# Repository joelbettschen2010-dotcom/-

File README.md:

> **Weitere Projekte in diesem Repo:** [🤠 Wild West — Minecraft-Mod](westernmod/) für
> Minecraft Java 1.21.1 (Fabric).

# 🚲 Velo Navi Schweiz

Eine Velo-/E-Bike-Navigations-App für die **ganze Schweiz**. Sie schlägt
mehrere Routen vor, berechnet die Fahrzeit **physikalisch** (inkl. Steigung
und Velo-Typ) und **lernt dein persönliches Tempo** aus deinem Feedback nach
jeder Fahrt.

Läuft als **einzelne Web-App ohne Server** – einfach `index.html` im Browser
öffnen (oder in der Claude-App als Vorschau).

## Funktionen

- **Ganze Schweiz** – Ortssuche über swisstopo/geo.admin.ch oder Klick auf die Karte.
- **Mehrere Routenvorschläge** – Alternativrouten + optional andere Fahrstile als Varianten.
- **Velo-Typ wählbar** – **Velo**, **E-Bike 25** (Abregelung 25 km/h),
  **E-Bike 45** (S-Pedelec, 45 km/h). Der Motor wird im Zeitmodell berücksichtigt.
- **Routen-Stil** – **Trekking/Stadt**, **Rennvelo**, **Gravel**, **MTB Trail**
  (eigene BRouter-Profile mit passenden Untergründen).
- **Höhenberechnung** – die Steigung jedes Streckenabschnitts fliesst in die Zeit ein
  (bergauf dauert länger, bergab schneller), mit Höhenprofil-Diagramm.
- **Routenbeschreibung** – Anteil Strasse / Veloweg / Schotter / Wald / Trail,
  Höhenmeter ↑↓ und maximale Steigung pro Route.
- **Tempo-Feedback & Kalibrierung** – nach jeder Fahrt angeben „war schneller/langsamer".
  Die App passt den Tempo-Faktor **pro Velo-Typ** an und speichert ihn lokal.
- **GPX-Export** je Route.

## Bedienung

1. `index.html` im Browser öffnen.
2. Start & Ziel eingeben (Suche) oder auf die Karte klicken.
3. Velo-Typ, Routen-Stil und Tretleistung wählen.
4. **Routen berechnen** drücken.
5. Eine Route anklicken → Karte + Höhenprofil. Mit **🏁 Gefahren** Feedback geben.

## Wie die Zeit berechnet wird

Pro Streckenabschnitt wird die Gleichgewichts­geschwindigkeit aus der
Leistungs­gleichung gelöst:

```
P = v · ( Crr·m·g·cosθ  +  m·g·sinθ  +  ½·ρ·CdA·v² ) / η
```

- `Crr` Rollwiderstand (je nach Untergrund: Asphalt … Trail)
- `m` Gesamtmasse (Fahrer + Velo, je nach Velo-Typ)
- `θ` Steigungswinkel aus den Höhendaten
- `CdA` Luftwiderstandsfläche, `ρ` Luftdichte, `η` Antriebs­wirkungsgrad
- `P` = Tretleistung **+ Motorleistung** (E-Bike, nur unterhalb der Abregelgeschwindigkeit)

Das Ergebnis wird mit deinem persönlichen **Kalibrierungs­faktor** multipliziert.

## Datenquellen

- **Karten:** [swisstopo](https://www.swisstopo.admin.ch) WMTS (Landeskarte / Satellit)
- **Routing & Höhen:** [BRouter](https://brouter.de) (OSM-basiert, kostenlos)
- **Ortssuche:** geo.admin.ch SearchServer
- **Karten-Engine:** [Leaflet](https://leafletjs.com)

Alle Dienste sind kostenlos und benötigen keinen API-Schlüssel. Es ist eine
Internet­verbindung nötig (Kacheln, Routing, Suche).

## Dateien

| Datei | Zweck |
|-------|-------|
| `index.html` | Aufbau / UI |
| `style.css` | Gestaltung (dunkles Theme, responsiv) |
| `app.js` | Karte, Routing, Zeitmodell, Höhenprofil, Feedback |

## Hinweise / Limiten

- Der öffentliche BRouter-Server hat eine Fair-Use-Begrenzung.
- Die berechnete Zeit ist eine Schätzung ohne Pausen; mit Feedback wird sie genauer.
- E-Bike-Reichweite/Akku wird (noch) nicht modelliert.

---

## Ebenfalls in diesem Repo

### 🏁 [Horizon Rush](game/) – Arcade-Rennspiel fürs iPhone

Prozedural erzeugte Strecken, adaptive Gegner-KI, Karriere, Garage und
Endlos-Marathon. Läuft im Browser, lässt sich über *Teilen → Zum
Home-Bildschirm* als Vollbild-App installieren und funktioniert offline.

**Spielen:** <https://joelbettschen2010-dotcom.github.io/-/game/>
· [Details](game/README.md)

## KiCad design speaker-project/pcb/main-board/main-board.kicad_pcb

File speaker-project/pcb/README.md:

# PCB — SpeakerBox Pro

Zwei Boards, vollständig aus Python-Design-Daten generiert (`design.py` je
Board = Netzliste, `generate.py` = Schaltplan + Layout via pcbnew-API).

| Board | Grösse | Inhalt |
|---|---|---|
| `main-board/` | 100 × 80 mm | 2× TPA3118D2 (BTL-Stereo + PBTL-Sub), ADAU1701-DSP, ESP32-S3, Power-Management, alle Anschlüsse |
| `button-board/` | 60 × 20 mm | 6 Taster (THT, 13-mm-Stössel), WS2812B, OLED-Header, JST-PH-8 |

## Verifizierte Design-Grundlagen

* **TPA3118D2**: Pinout + Gain-Tabelle + PBTL-Beschaltung aus TI SLOS708G.
  U6 = Master, Stereo-BTL, 20 dB (R 5.6 kΩ an GAIN/SLV). U7 = Slave, PBTL
  (LINP/LINN direkt an GND, Signal auf RINP, OUTPR+OUTNR = Plus-Klemme),
  20 dB Slave (51k/51k). SYNC-Bus verbindet beide (keine Schwebungstöne).
  Ausgangsfilter 10 µH + 680 nF (BD-Mode, 4 Ω).
* **ADAU1701**: 1.8-V-Core über externen PNP (BC807-40) an VDRIVE mit 1 kΩ
  (Datenblatt Fig. 16). PLL-Filter 475 Ω + 56 nF ∥ 3.3 nF an AVDD (Fig. 15).
  12.288-MHz-Quarz = 256×fs → PLL_MODE0=0, PLL_MODE1=1. ADC-Strom-Eingänge:
  18 kΩ Serie = 2 V rms Full-Scale, ADC_RES 18 kΩ. Selfboot mit 24LC32A.
* **Bluetooth**: BTM875-B (CSR8675, aptX HD) über 10-poligen Header,
  **analog** in die ADC-Eingänge gemischt (Aux + BT je 18 kΩ in denselben
  Strom-Eingang = passiver Mischer). Bewusst NICHT über I2S: der ADAU1701
  hat keine ASRC — asynchrones I2S vom BT-Modul erzeugt Klicks/Drift.
* **Fuel Gauge**: MAX17043/BQ27441 sind 1S-Gauges und können kein 4S-Pack
  messen → ersetzt durch Präzisionsteiler 100k/10k (1 %) auf ESP32-ADC.
* **Soft-Power**: 2× AO4407A (Verpolschutz + Schalter), Taster zieht Gate
  über Diode, ESP32 hält über NPN-Latch (PWR_HOLD), Soft-Start ~10 ms.
* **Buck**: LMR33630ADDA (36 V/3 A synchron) statt MP2315 — verifiziertes
  Pinout, mehr Spannungsreserve. FB-Teiler 100k/24.9k → 5.01 V.
* **Star-Ground**: AGND-Insel (DSP-Analogteil + Audio-Eingänge, unten
  links) trifft GND an genau einem Punkt (Net-Tie NT1).

## Routing-Status (ehrlich)

### Button-Board — ✅ FERTIG geroutet, DRC-sauber
Vollständig vom eigenen Grid-Router (`autoroute.py`) verdrahtet:
**0 offene Verbindungen, 0 Clearance-Verstöße, 0 nicht verbundene Pads**
(nur kosmetische Silk-Hinweise). Gerber liegt in `button-board/fab/` —
dieses Board kann **direkt bestellt** werden.

### Main-Board — ✅ FERTIG geroutet, DRC-sauber, bestellbar
4-Lagen-Design (F.Cu / **In1.Cu GND-Plane** / In2.Cu / B.Cu), vollständig
von **Freerouting** verdrahtet (lokaler Docker-Container, headless):

* **0 offene Verbindungen** (alle 524 Netz-Verbindungen geroutet)
* **0 elektrische DRC-Fehler** — keine Clearance-, Loch-, Kurzschluss-,
  Zonen- oder Breitenverstöße (verbleibende Meldungen sind kosmetisch:
  Silk-Text-Überlappungen der Auto-Platzierung, Bibliotheks-Metadaten,
  Courtyard-Mikroüberlappungen)
* ~2820 Bahnsegmente/Vias, 0.15-mm-Bahnen, 0.45/0.2-mm-Vias,
  Netzklasse 0.127 mm (JLCPCB-4-Lagen-Standard)
* GND zusätzlich als durchgehende In1-Plane + Füllungen auf F/In2/B

**Warum 4 Lagen:** Die Bauteildichte (ADAU1701 LQFP-48 mit 0.5 mm Pitch,
ESP32-S3-Modul, 2× TPA3118 HTSSOP, alle Stecker auf 100×80 mm) ist auf
2 Lagen nachweislich nicht vollständig routbar (getestet: ~71 offen).

**Werkzeugkette (alles im Repo, reproduzierbar):** KiCads
`ExportSpecctraDSN`/`ImportSpecctraSES` sind im headless Build defekt —
eigener DSN-Exporter (`dsn_export.py`) und SES-Importer (`ses_import.py`)
übergeben das Board an Freerouting und holen das Ergebnis zurück:

```bash
cd pcb && ./route_freerouting.sh          # Docker + ghcr.io/freerouting/freerouting
```

Wichtige Exporter-Details (hart erarbeitet): rotationsbewusste
Pad-Bounding-Boxen (`GetSize()` ignoriert Rotation!), quadratische Pads als
Rechteck statt Kreis (Ecken!), NPTH-Montagelöcher als netzlose Hindernisse
mit eindeutigen Referenzen, Keepouts (Taster-Hebel, ESP-Antenne) und das
NT1-Sternmasse-Polygon als Sperrflächen, gebohrte Pads auf
Loch+0.56 mm aufgeblasen (deckt KiCads 0.25-mm-Hole-Clearance),
`NETSHUF`-Netzreihenfolge für alternative Läufe, `WIRED=1` übergibt
vorhandene Verdrahtung zum Lückenschließen.

## Dateien

```
pcb/
├── schgen.py / pcbgen.py       gemeinsame Generator-Bibliothek
├── export_fab.sh               Gerber/Drill/Pos/SVG/BOM-Export
├── gen_bom.py                  JLCPCB-BOM-Generator
├── main-board/
│   ├── design.py               Netzliste (alle Verbindungen, LCSC-Nummern)
│   ├── generate.py             Platzierung + Zonen
│   ├── main-board.kicad_sch/.kicad_pcb/.kicad_pro
│   ├── drc-report.txt
│   └── fab/                    gerber.zip, BOM, positions.csv, SVG-Preview
└── button-board/               (analog)
```

Fertigungsparameter JLCPCB: Main-Board **4 Lagen**, Button-Board 2 Lagen;
FR4 1.6 mm, HASL bleifrei, 1 oz, grün; SMT-Bestückung Top-Seite (Economic),
THT-Stecker von Hand.

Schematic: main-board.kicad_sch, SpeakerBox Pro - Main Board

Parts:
C2, C3, C83, C84: 10u/25V; C_1206_3216Metric; LCSC C13585
C4, C5, C12, C18, C24, C25, C26, C27, C28, C29, C31, C50, C51, C52, C66, C75, C90: 100n; C_0603_1608Metric; LCSC C14663
C6, C48, C49, C64, C65, C73: 1u; C_0603_1608Metric; LCSC C15849
C7, C8, C74, C77: 22u; C_0805_2012Metric; LCSC C45783
C9, C10, C11, C19, C21, C23, C30: 10u; C_0805_2012Metric; LCSC C15850
C13, C14: 22p; C_0603_1608Metric; LCSC C1653
C15: 3n3; C_0603_1608Metric; LCSC C1594
C16: 56n; C_0603_1608Metric; LCSC C1621
C17: 47u; CP_Elec_6.3x7.7; LCSC C134801
C32, C33, C34, C35: 4u7; C_0805_2012Metric; LCSC C29823
C36, C37: 100p; C_0603_1608Metric; LCSC C14858
C38, C39, C40: 4n7; C_0603_1608Metric; LCSC C1590
C41, C42, C43, C45, C46, C63: 2u2; C_0805_2012Metric; LCSC C49217
C55, C56, C57, C58, C67, C68, C69, C70: 220n; C_0603_1608Metric; LCSC C21120
C59, C60, C61, C62, C71, C72: 680n/50V; C_0805_2012Metric; LCSC C28779
C76: 10n; C_0603_1608Metric; LCSC C57112
C80, C81, C82: 1000u/25V; CP_Elec_10x10.5; LCSC C249785
D1: SMBJ18A; D_SMB; LCSC C114213
D2, D3: BZT52C12; D_SOD-123; LCSC C110188
D4: 1N4148WS; D_SOD-323; LCSC C2128
D5: LED rt; LED_0603_1608Metric; LCSC C2286
D6, D7: LED gn; LED_0603_1608Metric; LCSC C72043
D8: SS34; D_SMA; LCSC C8678
F1: 10A; Fuse_1812_4532Metric; LCSC C369167
FB1, FB2: 600R@100MHz; L_0805_2012Metric; LCSC C1017
J1: XT30U-M; AMASS_XT30U-M_1x02_P5.0mm_Vertical
J2, J3: JST-XH-5; JST_XH_B5B-XH-A_1x05_P2.50mm_Vertical; LCSC C158012
J4: CHG-STAT; PinHeader_1x03_P2.54mm_Vertical; LCSC C2337
J5: ICP5/USBi; PinHeader_2x05_P2.54mm_Vertical; LCSC C2337
J6: AuxIn 3.5mm; Jack_3.5mm_CUI_SJ-3523-SMT_Horizontal; LCSC C145814
J7: FR-L; TerminalBlock_Phoenix_MKDS-1,5-2-5.08_1x02_P5.08mm_Horizont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; LCSC C8465
J8: FR-R; TerminalBlock_Phoenix_MKDS-1,5-2-5.08_1x02_P5.08mm_Horizont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; LCSC C8465
J9: SUB; TerminalBlock_Phoenix_MKDS-1,5-2-5.08_1x02_P5.08mm_Horizont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; LCSC C8465
J10: UART0; PinHeader_1x03_P2.54mm_Vertical; LCSC C2337
J11: USB-C; USB_C_Receptacle_HRO_TYPE-C-31-M-12; LCSC C165948
J12: JTAG; PinHeader_2x05_P1.27mm_Vertical_SMD; LCSC C2962219
J13: BT-Modul; PinHeader_1x10_P2.54mm_Vertical; LCSC C2337
J14: Button-PCB; JST_PH_B8B-PH-K_1x08_P2.00mm_Vertical; LCSC C157935
L1: 10uH/4A; L_6.3x6.3_H3; LCSC C167219
L2, L3, L4, L5: 10uH/5A; L_12x12mm_H8mm; LCSC C167221
L6, L7: 10uH/8A; L_12x12mm_H8mm; LCSC C167221
NT1: NetTie; NetTie-2_SMD_Pad2.0mm
Q1, Q2: AO4407A; SOIC-8_3.9x4.9mm_P1.27mm; LCSC C77843
Q3: MMBT3904; SOT-23; LCSC C20526
Q4: BC807-40; SOT-23; LCSC C130197
R1, R2, R30, R33, R36, R60, R61: 100k; R_0603_1608Metric; LCSC C25803
R3, R9, R18: 1k; R_0603_1608Metric; LCSC C21190
R4, R5, R6, R14, R19, R20, R31, R37, R38, R41, R62: 10k; R_0603_1608Metric; LCSC C25804
R7, R8: 4k7; R_0603_1608Metric; LCSC C23162
R10, R12: 100k 1%; R_0603_1608Metric; LCSC C25803
R11: 24k9 1%; R_0603_1608Metric; LCSC C23046
R13: 10k 1%; R_0603_1608Metric; LCSC C25804
R15: 100R; R_0603_1608Metric; LCSC C22775
R16: 475R 1%; R_0603_1608Metric; LCSC C23233
R17, R23, R24, R25, R26: 18k 1%; R_0603_1608Metric; LCSC C25810
R21, R22: 2k2; R_0603_1608Metric; LCSC C4190
R27, R28, R29: 560R; R_0603_1608Metric; LCSC C23204
R32: 5k6; R_0603_1608Metric; LCSC C23189
R34, R35: 51k; R_0603_1608Metric; LCSC C23196
R39, R40: 5k1; R_0603_1608Metric; LCSC C23186
R63: 0R; R_0603_1608Metric; LCSC C21189
SW1: RESET; SW_SPST_SKQG_WithStem; LCSC C221929
SW2: BOOT; SW_SPST_SKQG_WithStem; LCSC C221929
U1: LMR33630ADDA; Texas_HSOP-8-1EP_3.9x4.9mm_P1.27mm_ThermalVias; LCSC C841384
U2: AMS1117-3.3; SOT-223-3_TabPin2; LCSC C6186
U3: ADAU1701JSTZ; LQFP-48_7x7mm_P0.5mm; LCSC C51118
U4: 24LC32A; SOIC-8_3.9x4.9mm_P1.27mm; LCSC C7593
U6, U7: TPA3118D2DAP; HTSSOP-32-1EP_6.1x11mm_P0.65mm_EP5.2x11mm_Mask4.11x4.36mm_T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; LCSC C88243
U8: ESP32-S3-WROOM-1-N8R2; ESP32-S3-WROOM-1; LCSC C2913202
U9: USBLC6-2SC6; SOT-23-6; LCSC C7519
Y1: 12.288MHz; Crystal_SMD_3225-4Pin_3.2x2.5mm; LCSC C255909

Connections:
3V3: C10.1, C28.1, C30.1, C31.1, C74.1, C75.1, FB1.1, FB2.1, J5.1 (3V3), J12.1 (3V3), J14.3 (3V3), Q4.2 (E), R6.2, R9.2, R14.2, R19.2, R20.2, R21.2, R22.2, R31.2, R37.2, R38.2, R41.2, R60.2, R61.2, R63.2, U2.2 (VOUT), U3.18 (IOVDD), U3.39 (PLL_MODE1), U4.8 (VCC), U8.2 (3V3)
3V3A: C11.1, C15.2, C16.2, C26.1, C27.1, FB1.2, U3.36 (AVDD), U3.48 (AVDD)
3V3_BT: C77.1, FB2.2, J13.1 (3V3)
5V: C7.1, C8.1, C9.1, D8.1 (K), J14.1 (5V), L1.2, R10.2, U2.3 (VIN)
ADC0_IN: C36.1, R23.2, R25.2, U3.2 (ADC0)
ADC1_IN: C37.1, R24.2, R26.2, U3.4 (ADC1)
ADCRES: R17.1, U3.3 (ADC_RES)
ADDR1: J5.7 (WB), R62.1, U3.20 (ADDR1/WB)
AGND: C11.2, C17.2 (-), C18.2, C19.2, C21.2, C26.2, C27.2, C36.2, C37.2, C38.2, C39.2, C40.2, C45.2, C46.2, C63.2, J6.1 (SLEEVE), J13.5 (AGND), NT1.1 (A), R17.2, U3.1 (AGND), U3.37 (AGND), U3.42 (AGND)
AMPIN_L: C41.2, U6.10 (LINP)
AMPIN_R: C42.2, U6.4 (RINP)
AMPIN_SUB: C43.2, U7.4 (RINP)
AMP_FAULT: R31.1, U6.3 (FAULTZ), U7.3 (FAULTZ), U8.24 (IO47)
AMP_MUTE: R33.1, R36.1, U6.12 (MUTE), U7.12 (MUTE), U8.23 (IO21)
AMP_SDZ: R30.1, U6.2 (SDZ), U7.2 (SDZ), U8.8 (IO15)
AUXC_L: C32.2, R23.1
AUXC_R: C33.2, R24.1
AUX_L: C32.1, J6.2 (TIP)
AUX_R: C33.1, J6.3 (RING)
BAL1: J2.2 (C1), J3.2 (C1)
BAL2: J2.3 (C2), J3.3 (C2)
BAL3: J2.4 (C3), J3.4 (C3)
BTC_L: C34.2, R25.1
BTC_R: C35.2, R26.1
BTN_ADC: C76.1, J14.7 (BTN), R41.1, U8.6 (IO6)
BTN_PWR: D4.1 (K), J14.8 (PWR), R6.1, U8.5 (IO5)
BT_EN: J13.10 (EN), U8.15 (IO3)
BT_L: C34.1, J13.3 (AOUT_L)
BT_PAIR: J13.9 (PAIR), U8.19 (IO11)
BT_R: C35.1, J13.4 (AOUT_R)
BT_RXD: J13.6 (MOD_TX), U8.11 (IO18)
BT_STATUS: J13.8 (STATUS), U8.18 (IO10)
BT_TXD: J13.7 (MOD_RX), U8.10 (IO17)
CC1: J11.A5 (CC1), R39.1
CC2: J11.B5 (CC2), R40.1
CHG_STAT: D5.1 (K), J4.1 (CHG), R60.1, U8.20 (IO12)
CM: C17.1 (+), C18.1, U3.40 (CM)
D5_A: D5.2 (A), R7.1
D6_A: D6.2 (A), R8.1
D7_A: D7.2 (A), R9.1
DACF_L: C38.1, C41.1, R27.2
DACF_R: C39.1, C42.1, R28.2
DACF_SUB: C40.1, C43.1, R29.2
DAC_L: R27.1, U3.46 (VOUT0)
DAC_R: R28.1, U3.45 (VOUT1)
DAC_SUB: R29.1, U3.44 (VOUT2)
DSP_NRST: J5.5 (~RST), R19.1, U3.5 (~RESET), U8.25 (IO48)
DVDD_1V8: C23.1, C24.1, C25.1, Q4.3 (C), U3.13 (DVDD), U3.24 (DVDD)
EE_WP: J5.8 (WP), R20.1, U3.21 (CLATCH/WP), U4.7 (WP)
ESP_BOOT: R38.1, SW2.1, SW2.2 (1), U8.27 (IO0)
ESP_EN: C73.1, J12.10 (EN), R37.1, SW1.1, SW1.2 (1), U8.3 (EN)
FB5V: R10.1, R11.1, U1.5 (FB)
FILTA: C21.1, U3.47 (FILTA)
FILTD: C19.1, U3.41 (FILTD)
FR_L_N: C60.1, J7.2 (-), L3.2
FR_L_P: C59.1, J7.1 (+), L2.2
FR_R_N: C62.1, J8.2 (-), L5.2
FR_R_P: C61.1, J8.1 (+), L4.2
FULL_STAT: D6.1 (K), J4.2 (FULL), R61.1, U8.21 (IO13)
GND: C2.2, C3.2, C4.2, C6.2, C7.2, C8.2, C9.2, C10.2, C12.2, C13.2, C14.2, C23.2, C24.2, C25.2, C28.2, C29.2, C30.2, C31.2, C48.2, C49.2, C50.2, C51.2, C52.2, C59.2, C60.2, C61.2, C62.2, C64.2, C65.2, C66.2, C71.2, C72.2, C73.2, C74.2, C75.2, C76.2, C77.2, C80.2 (-), C81.2 (-), C82.2 (-), C83.2, C84.2, D1.2 (A), D7.1 (K), J1.2 (BAT-), J2.1 (B-), J3.1 (B-), J4.3 (GND), J5.2 (GND), J5.10 (GND), J10.3 (GND), J11.A1 (GND), J11.A12 (GND), J11.B1 (GND), J11.B12 (GND), J11.S1 (SHIELD), J12.3 (GND), J12.5 (GND), J12.9 (GND), J13.2 (GND), J14.2 (GND), NT1.2 (B), Q3.2 (E), R1.2, R5.2, R11.2, R13.2, R30.2, R32.2, R34.2, R39.2, R40.2, R62.2, SW1.3 (2), SW1.4 (2), SW2.3 (2), SW2.4 (2), U1.1 (GND), U1.9 (EP), U2.1 (GND)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
GVDD1: C48.1, R33.2, U6.6 (PLIMIT), U6.7 (GVDD)
GVDD2: C64.1, R35.2, R36.2, U7.6 (PLIMIT), U7.7 (GVDD)
JTAG_MTCK: J12.4 (MTCK), U8.32 (IO39)
JTAG_MTDI: J12.8 (MTDI), U8.34 (IO41)
JTAG_MTDO: J12.6 (MTDO), U8.33 (IO40)
JTAG_MTMS: J12.2 (MTMS), U8.35 (IO42)
LED_DATA: J14.6 (LED), U8.9 (IO16)
MCLKI: C13.1, U3.32 (MCLKI), Y1.1 (X1)
OSCO: R15.1, U3.31 (OSCO)
OSC_D: C14.1, R15.2, Y1.3 (X2)
PLLRC: C16.1, R16.2
PLL_LF: C15.1, R16.1, U3.35 (PLL_LF)
PVDD: C2.1, C3.1, C4.1, C49.1, C50.1, C51.1, C52.1, C65.1, C66.1, C80.1 (+), C81.1 (+), C82.1 (+), C83.1, C84.1, Q2.5 (D), Q2.6 (D), Q2.7 (D), Q2.8 (D), U1.2 (VIN), U1.3 (EN), U6.17 (AVCC), U6.18 (PVCC), U6.19 (PVCC), U6.31 (PVCC), U6.32 (PVCC), U7.17 (AVCC), U7.18 (PVCC), U7.19 (PVCC), U7.31 (PVCC), U7.32 (PVCC)
PVDD_PLL: C29.1, R63.1, U3.34 (PVDD)
PWR_CTL: D4.2 (A), Q3.3 (C), R3.2
PWR_HOLD: R4.2, U8.4 (IO4)
Q1_G: D2.2 (A), Q1.4 (G), R1.1
Q2_G: C90.1, D3.2 (A), Q2.4 (G), R2.1, R3.1
Q3_B: Q3.1 (B), R4.1, R5.1
SCL: J5.3 (SCL), J14.5 (SCL), R22.1, U3.23 (SCL), U4.6 (SCL), U8.17 (IO9)
SDA: J5.4 (SDA), J14.4 (SDA), R21.1, U3.22 (SDA), U4.5 (SDA), U8.12 (IO8)
SELFBOOT: J5.6 (SELFBOOT), R14.1, U3.6 (SELFBOOT)
SUB_N: C72.1, J9.2 (-), L7.2
SUB_OUT_N: C67.2, C68.2, L7.1, U7.21 (OUTNL), U7.23 (OUTPL)
SUB_OUT_P: C69.2, C70.2, L6.1, U7.27 (OUTNR), U7.29 (OUTPR)
SUB_P: C71.1, J9.1 (+), L6.2
SW5V: C5.2, L1.1, U1.8 (SW)
SYNC: U6.16 (SYNC), U7.16 (SYNC)
U1_BOOT: C5.1, U1.7 (BOOT)
U1_VCC: C6.1, U1.6 (VCC)
U6_BSNL: C55.1, U6.20 (BSNL)
U6_BSNR: C57.1, U6.26 (BSNR)
U6_BSPL: C56.1, U6.24 (BSPL)
U6_BSPR: C58.1, U6.30 (BSPR)
U6_GAIN: R32.1, U6.8 (GAIN/SLV)
U6_LINN: C46.1, U6.11 (LINN)
U6_OUTNL: C55.2, L3.1, U6.21 (OUTNL)
U6_OUTNR: C57.2, L5.1, U6.27 (OUTNR)
U6_OUTPL: C56.2, L2.1, U6.23 (OUTPL)
U6_OUTPR: C58.2, L4.1, U6.29 (OUTPR)
U6_RINN: C45.1, U6.5 (RINN)
U7_BSNL: C67.1, U7.20 (BSNL)
U7_BSNR: C69.1, U7.26 (BSNR)
U7_BSPL: C68.1, U7.24 (BSPL)
U7_BSPR: C70.1, U7.30 (BSPR)
U7_GAIN: R34.1, R35.1, U7.8 (GAIN/SLV)
U7_RINN: C63.1, U7.5 (RINN)
UART0_RX: J10.2 (RX), U8.36 (RXD0)
UART0_TX: J10.1 (TX), U8.37 (TXD0)
USB_DN: J11.A7 (D-), J11.B7 (D-), U8.13 (IO19), U9.1 (IO1), U9.6 (IO1b)
USB_DP: J11.A6 (D+), J11.B6 (D+), U8.14 (IO20), U9.3 (IO2), U9.4 (IO2b)
VBAT_F: D1.1 (K), F1.2, Q1.5 (D), Q1.6 (D), Q1.7 (D), Q1.8 (D)
VBAT_P: C90.2, D2.1 (K), D3.1 (K), Q1.1 (S), Q1.2 (S), Q1.3 (S), Q2.1 (S), Q2.2 (S), Q2.3 (S), R2.2, R7.2, R8.2, R12.1
VBAT_RAW: F1.1, J1.1 (BAT+), J2.5 (B+), J3.5 (B+)
VBSENSE: C12.1, R12.2, R13.1, U8.7 (IO7)
VBUS: D8.2 (A), J11.A4 (VBUS), J11.A9 (VBUS), J11.B4 (VBUS), J11.B9 (VBUS), U9.5 (VBUS)
VDRIVE: R18.1, U3.17 (VDRIVE)
VDRV_B: Q4.1 (B), R18.2

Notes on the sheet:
POWER INPUT + SOFT SWITCH
5V BUCK + 3V3 LDO
DSP ADAU1701
AUDIO IN + DAC OUT
AMP FULLRANGE (U6 Master BTL)
AMP SUB (U7 Slave PBTL)
ESP32-S3 + USB + DEBUG
BLUETOOTH + CONNECTORS

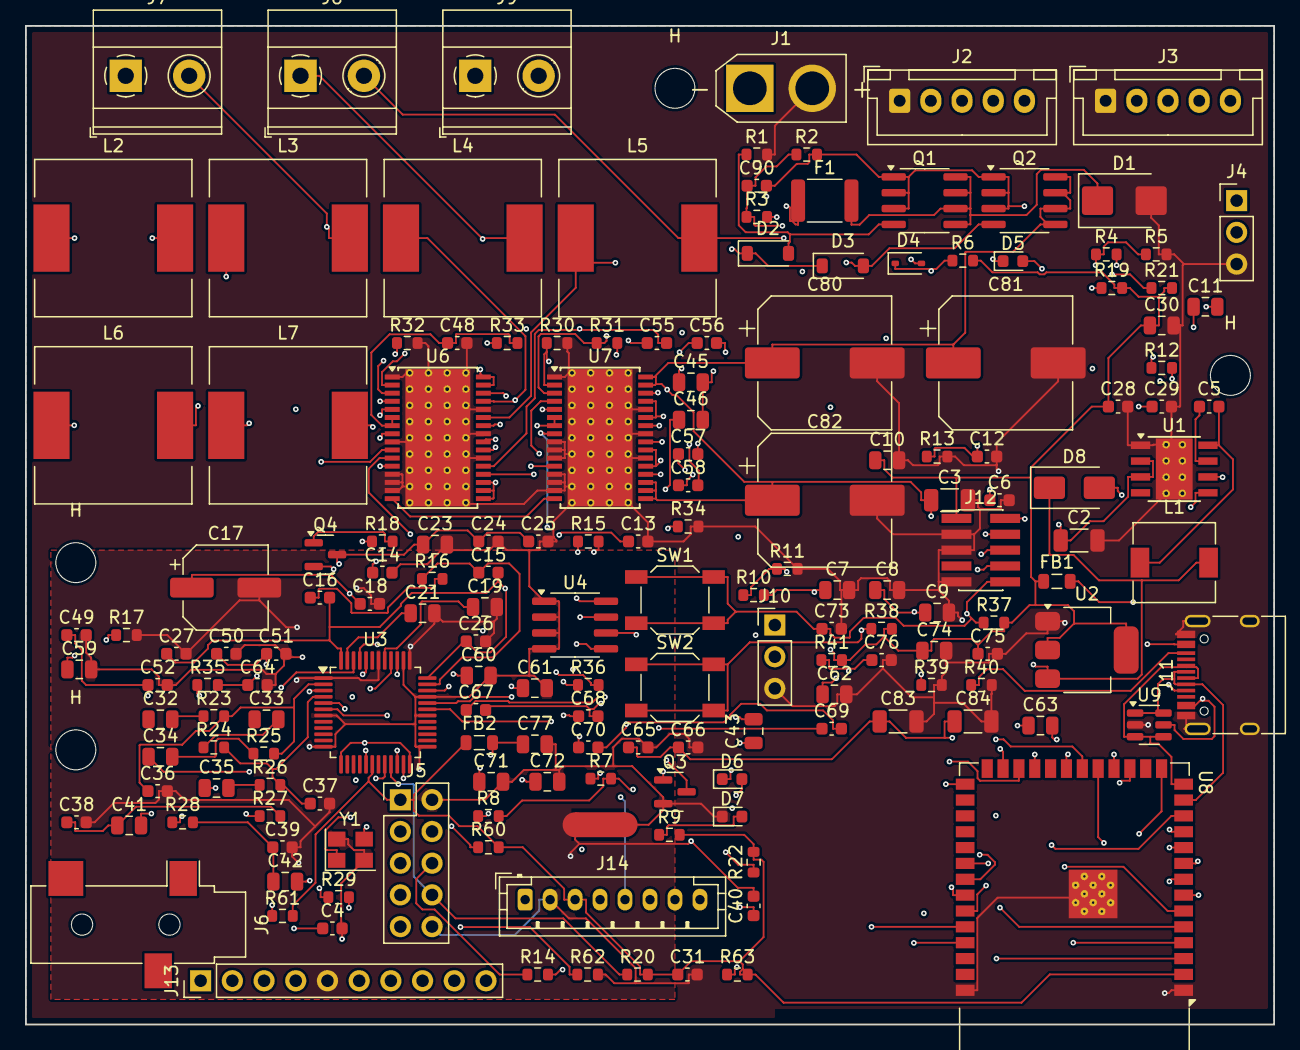
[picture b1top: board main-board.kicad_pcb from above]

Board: 4 copper layers, 100.0 x 80.0 mm, 173 parts (0 on the bottom side), 116 nets.

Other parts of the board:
H: MountingHole_3.2mm_M3
H#2, H#3, H#4: MountingHole_3.2mm_M3

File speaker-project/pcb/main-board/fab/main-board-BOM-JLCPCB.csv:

Comment,Designator,Footprint,LCSC Part #
22p,"C13,C14",C_0603_1608Metric,C1653
3n3,C15,C_0603_1608Metric,C1594
56n,C16,C_0603_1608Metric,C1621
47u,C17,CP_Elec_6.3x7.7,C134801
10u/25V,"C2,C3,C83,C84",C_1206_3216Metric,C13585
4u7,"C32,C33,C34,C35",C_0805_2012Metric,C29823
100p,"C36,C37",C_0603_1608Metric,C14858
4n7,"C38,C39,C40",C_0603_1608Metric,C1590
2u2,"C41,C42,C43,C45,C46,C63",C_0805_2012Metric,C49217
220n,"C55,C56,C57,C58,C67,C68,C69,C70",C_0603_1608Metric,C21120
680n/50V,"C59,C60,C61,C62,C71,C72",C_0805_2012Metric,C28779
1u,"C48,C49,C6,C64,C65,C73",C_0603_1608Metric,C15849
22u,"C7,C74,C77,C8",C_0805_2012Metric,C45783
10n,C76,C_0603_1608Metric,C57112
1000u/25V,"C80,C81,C82",CP_Elec_10x10.5,C249785
10u,"C10,C11,C19,C21,C23,C30,C9",C_0805_2012Metric,C15850
100n,"C12,C18,C24,C25,C26,C27,C28,C29,C31,C4,C5,C50,C51,C52,C66,C75,C90",C_0603_1608Metric,C14663
SMBJ18A,D1,D_SMB,C114213
BZT52C12,"D2,D3",D_SOD-123,C110188
1N4148WS,D4,D_SOD-323,C2128
LED rt,D5,LED_0603_1608Metric,C2286
LED gn,"D6,D7",LED_0603_1608Metric,C72043
SS34,D8,D_SMA,C8678
10A,F1,Fuse_1812_4532Metric,C369167
600R@100MHz,"FB1,FB2",L_0805_2012Metric,C1017
XT30U-M,J1,AMASS_XT30U-M_1x02_P5.0mm_Vertical,
UART0,J10,PinHeader_1x03_P2.54mm_Vertical,C2337
USB-C,J11,USB_C_Receptacle_HRO_TYPE-C-31-M-12,C165948
JTAG,J12,PinHeader_2x05_P1.27mm_Vertical_SMD,C2962219
BT-Modul,J13,PinHeader_1x10_P2.54mm_Vertical,C2337
Button-PCB,J14,JST_PH_B8B-PH-K_1x08_P2.00mm_Vertical,C157935
JST-XH-5,"J2,J3",JST_XH_B5B-XH-A_1x05_P2.50mm_Vertical,C158012
CHG-STAT,J4,PinHeader_1x03_P2.54mm_Vertical,C2337
ICP5/USBi,J5,PinHeader_2x05_P2.54mm_Vertical,C2337
AuxIn 3.5mm,J6,Jack_3.5mm_CUI_SJ-3523-SMT_Horizontal,C145814
FR-L,J7,"TerminalBlock_Phoenix_MKDS-1,5-2-5.08_1x02_P5.08mm_Horizontal",C8465
FR-R,J8,"TerminalBlock_Phoenix_MKDS-1,5-2-5.08_1x02_P5.08mm_Horizontal",C8465
SUB,J9,"TerminalBlock_Phoenix_MKDS-1,5-2-5.08_1x02_P5.08mm_Horizontal",C8465
10uH/4A,L1,L_6.3x6.3_H3,C167219
10uH/5A,"L2,L3,L4,L5",L_12x12mm_H8mm,C167221
10uH/8A,"L6,L7",L_12x12mm_H8mm,C167221
NetTie,NT1,NetTie-2_SMD_Pad2.0mm,
AO4407A,"Q1,Q2",SOIC-8_3.9x4.9mm_P1.27mm,C77843
MMBT3904,Q3,SOT-23,C20526
BC807-40,Q4,SOT-23,C130197
100k,"R1,R2,R30,R33,R36,R60,R61",R_0603_1608Metric,C25803
100k 1%,"R10,R12",R_0603_1608Metric,C25803
24k9 1%,R11,R_0603_1608Metric,C23046
10k 1%,R13,R_0603_1608Metric,C25804
100R,R15,R_0603_1608Metric,C22775
475R 1%,R16,R_0603_1608Metric,C23233
18k 1%,"R17,R23,R24,R25,R26",R_0603_1608Metric,C25810
2k2,"R21,R22",R_0603_1608Metric,C4190
560R,"R27,R28,R29",R_0603_1608Metric,C23204
1k,"R18,R3,R9",R_0603_1608Metric,C21190
5k6,R32,R_0603_1608Metric,C23189
51k,"R34,R35",R_0603_1608Metric,C23196
5k1,"R39,R40",R_0603_1608Metric,C23186
10k,"R14,R19,R20,R31,R37,R38,R4,R41,R5,R6,R62",R_0603_1608Metric,C25804
0R,R63,R_0603_1608Metric,C21189
4k7,"R7,R8",R_0603_1608Metric,C23162
RESET,SW1,SW_SPST_SKQG_WithStem,C221929
BOOT,SW2,SW_SPST_SKQG_WithStem,C221929
LMR33630ADDA,U1,Texas_HSOP-8-1EP_3.9x4.9mm_P1.27mm_ThermalVias,C841384
AMS1117-3.3,U2,SOT-223-3_TabPin2,C6186
ADAU1701JSTZ,U3,LQFP-48_7x7mm_P0.5mm,C51118
24LC32A,U4,SOIC-8_3.9x4.9mm_P1.27mm,C7593
TPA3118D2DAP,"U6,U7",HTSSOP-32-1EP_6.1x11mm_P0.65mm_EP5.2x11mm_Mask4.11x4.36mm_ThermalVias,C88243
ESP32-S3-WROOM-1-N8R2,U8,ESP32-S3-WROOM-1,C2913202
USBLC6-2SC6,U9,SOT-23-6,C7519
12.288MHz,Y1,Crystal_SMD_3225-4Pin_3.2x2.5mm,C255909

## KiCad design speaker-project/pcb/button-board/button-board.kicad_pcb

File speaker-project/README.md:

# SpeakerBox Pro

Custom 2.1-Bluetooth-Lautsprecher: 2× Dayton ND91-4 (3.5"-Fullrange) +
Dayton TCP115-4 (4"-Sub), ADAU1701-DSP, 2× TPA3118, ESP32-S3 mit
PWA-Steuerung, 4S2P-18650-Akku, 3D-gedrucktes Gehäuse mit drei
geschlossenen Kammern.

## Projektstruktur

| Ordner | Inhalt | Status |
|---|---|---|
| `acoustics/` | T/S-Simulation, Volumen-Sweep, Crossover-Optimierung + Plots | ✅ läuft, Plots generiert |
| `dsp/` | ADAU1701-Programmgenerator, Parameter-XML, 3 Presets, Doku | ✅ generiert |
| `pcb/main-board/` | Haupt-PCB 100×80, **4-Lagen** (Amps, DSP, ESP32, Power) | ✅ **FERTIG geroutet: 0 offene Verbindungen, 0 elektrische DRC-Fehler — bestellbar** (4-Lagen, Freerouting, ~2820 Bahnen/Vias) |
| `pcb/button-board/` | Bedien-PCB 60×20 (Taster, RGB-LED, OLED) | ✅ **vollständig geroutet, DRC-sauber, bestellbar** |
| `firmware/` | ESP32-S3 PlatformIO | ✅ kompiliert (`pio run` SUCCESS) |
| `webapp/` | Next.js-14-PWA (Dashboard, EQ, Settings, Info) | ✅ baut (`npm run build`), läuft vom ESP32 |
| `docs/` | BOM/Kosten, Montage-Anleitung, Debugging-Guide | ✅ |

## Kernergebnisse der Simulation

* Treiber: **Dayton ND91-4** (Fs 74 Hz, Qts 0.41, Xmax 4.6 mm) und
  **Dayton TCP115-4** (Fs 53.8 Hz, Qts 0.35, Xmax 4+ mm) — Datenblattwerte,
  vor der finalen Abstimmung am realen Chassis nachmessen.
* Fullrange-Kammern 0.38 L netto (+Dämmwolle) → Fc 152 Hz, Qtc 0.84,
  f3 ≈ 132 Hz; Sub-Kammer 1.9 L netto (+Dämmwolle) → Fc 84 Hz, Qtc 0.54,
  f3 ≈ 115 Hz (mit DSP-Bass-Shelf tiefer spielbar, grosser Hub-Headroom).
* **Crossover: Linkwitz-Riley 12 dB/Okt @ 310 Hz**, Sub invertiert,
  1.10 ms Delay (Optimum aus komplexem Summen-Sweep, Rest-Welligkeit
  1.4 dB; der Vorgabebereich 150–180 Hz ist wegen der Einbauresonanz der
  kleinen Kammern physikalisch ungünstig).
* Max-SPL-Abschätzung System ~103–106 dB @ 1 m.

## Wichtige Design-Abweichungen (begründet)

* **BT-Audio analog statt I2S** in den DSP: der ADAU1701 hat keine ASRC,
  asynchrones I2S vom BT-Modul erzeugt Klicks. Analog über die
  ADC-Strom-Eingänge ist die etablierte Lösung (Details `pcb/README.md`).
* **MAX17043/BQ27441 entfallen**: das sind 1S-Fuel-Gauges, ungeeignet für
  4S. Ersatz: Präzisionsteiler + ESP32-ADC + OCV-Kennlinie.
* **MP2315 → LMR33630**: verifiziertes Pinout, 36-V-Reserve.
* **Buttons als Widerstandsleiter** (5 Tasten auf 1 ADC-Pin), Power-Taster
  separat (muss bei ausgeschaltetem ESP32 funktionieren).

## Reproduzieren

```bash
cd acoustics && python3 01_volume_sweep.py && python3 02_frequency_response.py && python3 03_crossover_optimization.py
cd dsp && python3 generate_dsp_program.py
cd pcb/main-board && python3 generate.py && cd ../button-board && python3 generate.py
cd pcb && ./export_fab.sh
cd firmware && pio run
cd webapp && npm install && npm run build && cp -r out/* ../firmware/data/www/
```

## Was noch von Hand zu tun ist

1. **Bestellen**: beide Gerber-ZIPs (`pcb/*/fab/*-gerber.zip`) bei JLCPCB
   hochladen (Main = 4-Lagen, Button = 2-Lagen), BOM + Positions-CSV für
   die SMT-Bestückung dazu. Treiber bei SoundImports, Module s. `docs/BOM.md`.
2. Reale T/S-Parameter der gelieferten Dayton-Treiber messen und die
   Simulation damit erneut laufen lassen (Crossover-Werte prüfen).
3. SigmaStudio-Projekt nach `dsp/README.md` aufbauen und EEPROM flashen.
4. Gehäuse drucken (K1-Dreiteiler), Montage nach `docs/montage-anleitung.md`,
   REW-Abstimmung.

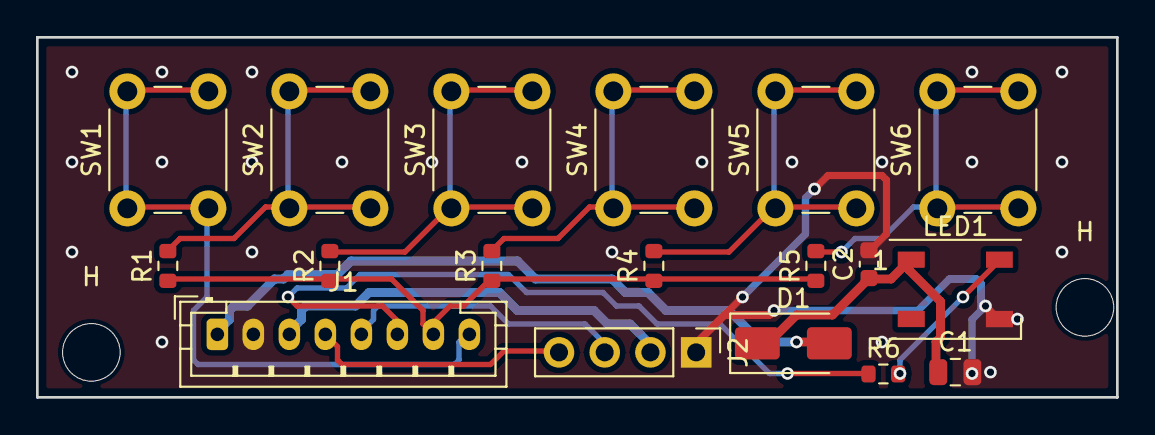
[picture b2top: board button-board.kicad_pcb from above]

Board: 2 copper layers, 60.0 x 20.0 mm, 20 parts (0 on the bottom side), 15 nets.

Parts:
C1: 22u; C_0805_2012Metric
C2: 100n; C_0603_1608Metric
D1: SS14; D_SMA
H: MountingHole_3.2mm_M3
H#2: MountingHole_3.2mm_M3
J1: zum Main-Board; JST_PH_B8B-PH-K_1x08_P2.00mm_Vertical
J2: OLED 0.96; PinHeader_1x04_P2.54mm_Vertical
LED1: WS2812B; LED_WS2812B_PLCC4_5.0x5.0mm_P3.2mm
R1: 0R; R_0603_1608Metric
R2: 2k2; R_0603_1608Metric
R3: 4k7; R_0603_1608Metric
R4: 10k; R_0603_1608Metric
R5: 22k; R_0603_1608Metric
R6: 330R; R_0603_1608Metric
SW1: POWER; SW_PUSH_6mm_H13mm
SW2: VOL+; SW_PUSH_6mm_H13mm
SW3: VOL-; SW_PUSH_6mm_H13mm
SW4: BT; SW_PUSH_6mm_H13mm
SW5: PLAY; SW_PUSH_6mm_H13mm
SW6: NEXT; SW_PUSH_6mm_H13mm

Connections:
3V3: J1.3, J2.2
5V: D1.2, J1.1
BTN_ADC: J1.7, R1.1, R2.1, R3.1, R4.1, R5.1
BTN_PWR: J1.8, SW1.1, SW1.2
GND: C1.2, C2.2, J1.2, J2.1, LED1.3
LAD0: R1.2, SW2.1, SW2.2
LAD1: R2.2, SW3.1, SW3.2
LAD2: R3.2, SW4.1, SW4.2
LAD3: R4.2, SW5.1, SW5.2
LAD4: R5.2, SW6.1, SW6.2
LED_DATA: J1.6, R6.1
LED_DIN: LED1.4, R6.2
LED_VDD: C1.1, C2.1, D1.1, LED1.1
SCL: J1.5, J2.3
SDA: J1.4, J2.4

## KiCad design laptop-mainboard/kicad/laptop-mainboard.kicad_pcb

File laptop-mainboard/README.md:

# Laptop-Mainboard — AMD AM5 im HP-EliteBook-850-G7-Chassis (Rev B)

Komplettes KiCad-8-Projekt für ein Laptop-Mainboard mit **gesockelter**
Desktop-CPU (AM5) statt verlöteter Mobile-CPU.

## Eckdaten

| Bereich | Umsetzung |
|---|---|
| CPU | **AMD Ryzen 5 8600G** (x86-64, Zen 4, 6C/12T, Radeon 760M) im **AM5-Sockel LGA-1718** — wechselbar wie beim Desktop-PC, per cTDP auf 35–45 W gedrosselt |
| Chipsatz | **keiner** (chipsatzlos wie DeskMini X600) — alle I/O direkt vom SoC |
| Pinbelegung | **alle 1718 AM5-Pins benannt** (docs/am5_pinmap.csv, WikiChip/Wikimedia Public Domain); 1708 Sockelpads im Board mit echtem Signal-Netz |
| RAM | 2× DDR5 **SO-DIMM** (1 DIMM pro Kanal, bis DDR5-5600, max. 96 GB) |
| Storage | 2× **M.2 2280 NVMe**, je PCIe 4.0 ×4, getrennt schaltbare 3.3-V-Schienen |
| WLAN | 1× M.2 2230 E-Key (PCIe ×1 + USB 2.0), z. B. Wi-Fi 7 Modul |
| Thunderbolt | 2× **Thunderbolt 4** über **Intel JHL8540** (Maple Ridge), PCIe ×4 Uplink + 2× DP-1.4-Sink |
| Laden | **Eigener USB-C-Ladeport** (100 W USB-PD, TPS65987D) an der Barrel-Jack-Position → **BQ25731** → HP-Akku 3S/56 Wh (NVDC) |
| USB | 2× USB-A 5 Gbit (je einer links/rechts, wie 850 G7) |
| Netzwerk | WLAN/BT über M.2-Modul (das Original hat kein RJ45) |
| Video | HDMI 2.1 (nativ vom SoC, TPD12S016-Companion), intern eDP 1.4 (2 Lanes) |
| Audio | Realtek ALC256, 3.5-mm-Kombiklinke (AUX), 2× 2-W-Lautsprecher |
| Kleinteile | Blatt 10: MLCC-Bänke, 11 ESD-Arrays, USB2-Chokes, Straps (beidseitige Bestückung) |
| EC | ITE IT5570E: Power-Sequencing, Tastatur 8×18, Akku-SMBus, 2× Lüfter |
| Board | 340 × 112 mm, 8 Lagen, Portlayout/Umriss für HP EliteBook 850 G7 (docs/elitebook.md) |

## Projektstruktur

```
laptop-mainboard/
├── kicad/                     KiCad-8-Projekt (öffnen: laptop-mainboard.kicad_pro)
│   ├── laptop-mainboard.kicad_sch   Übersichtsblatt (Hierarchie)
│   ├── 01_power_pd.kicad_sch        USB-PD, Laderegler, Systemschienen
│   ├── 02_vrm_cpu.kicad_sch         CPU-VRM (SVI3, 4+2 Phasen)
│   ├── 03_cpu_am5.kicad_sch         AM5-Sockel, BIOS-Flash, RTC
│   ├── 04_memory.kicad_sch          2× DDR5 SO-DIMM
│   ├── 05_storage.kicad_sch         2× M.2 NVMe + WLAN
│   ├── 06_usb_tb4.kicad_sch         Thunderbolt 4 + USB
│   ├── 07_ladeport.kicad_sch        USB-C-Ladeport 100W (TPS65987D)
│   ├── 08_display.kicad_sch         eDP, HDMI, Backlight, Webcam
│   ├── 09_audio_sd_ec.kicad_sch     Audio, Embedded Controller
│   ├── 10_kleinteile.kicad_sch      Entkopplung, ESD, Filter, Straps
│   ├── laptop-mainboard.kicad_pcb   Board: Umriss, Platzierung, Lagen, Zonen
│   ├── lm.kicad_sym                 Symbolbibliothek
│   └── laptop_mainboard.pretty/     Footprints (inkl. LGA-1718, SO-DIMM 262)
├── docs/
│   ├── architektur.md         Blockdiagramm, PCIe-/USB-/Display-Budget
│   ├── power.md               Schienen, Power-Budget, Sequencing
│   ├── layout.md              Lagenaufbau, Floorplan, Routing-Regeln
│   ├── elitebook.md           EliteBook-850-G7-Einbau: passt/zu messen
│   ├── am5_pinmap.csv         Alle 1718 AM5-Pins mit Signalnamen
│   ├── grenzen.md             Was dieses Projekt (bewusst) nicht abdeckt
│   ├── board_render.png       Bestückungsansicht (generiert)
│   └── bom.csv                Stückliste (150 Positionen)
└── tools/
    └── gen_all.py             Generator — erzeugt alle KiCad-Dateien
```

**Wichtig:** Die KiCad-Dateien werden generiert. Änderungen in
`tools/kicadgen/boarddata*.py` (Schaltung) bzw. `tools/gen_all.py`
(Floorplan) vornehmen und `python3 tools/gen_all.py` ausführen.

## Warum diese Architektur?

- **Gesockelte CPU:** AMD verkauft Mobile-CPUs nur als BGA (verlötet). Der
  Wunsch „normaler PC-Sockel statt löten" führt zwingend zum Desktop-Sockel
  AM5. Der Ryzen 5 8600G ist die effizienteste AM5-Wahl: monolithischer
  Phoenix-Die (kein Chiplet-Idle-Verbrauch), starke iGPU, offizieller
  cTDP-Bereich 35–65 W.
- **Chipsatzlos:** Ein B650-Chipsatz würde ~7 W dauerhaft verbrauchen. Der
  8600G hat genug eigene Lanes/USB-Ports für alle geforderten Anschlüsse.
- **Echtes Thunderbolt 4:** AMD kann nur USB4. Für zertifizierbares TB4 sitzt
  ein Intel JHL8540 auf dem Board (PCIe ×4 + 2× DisplayPort vom SoC).
- **NVDC-Laden:** Der BQ25731 lässt das System direkt aus dem 100-W-Netzteil
  laufen und lädt den Akku mit dem Rest — Standard-Topologie moderner Laptops.

## Ehrlichkeit / Reifegrad

Rev B ist ein **weit ausgearbeiteter Prototyp-Stand**: vollständige
Systemarchitektur, echte AM5-Pinbelegung (Public-Domain-Quelle) an allen
Sockelpads, Kleinteile (Entkopplung/ESD/Filter) auf eigenem Blatt,
kollisionsfreier beidseitiger Floorplan im EliteBook-Format mit Zonen,
Stitching-Vias und Routing-Korridoren. **Noch nicht bestellbar:** das
DRC-saubere Feinrouting aller ~640 Netze, die Verifikation der
Community-Pinmap und die HP-Mechanik-/FPC-Vermessung stehen aus —
Details in [docs/grenzen.md](docs/grenzen.md) und
[docs/elitebook.md](docs/elitebook.md).

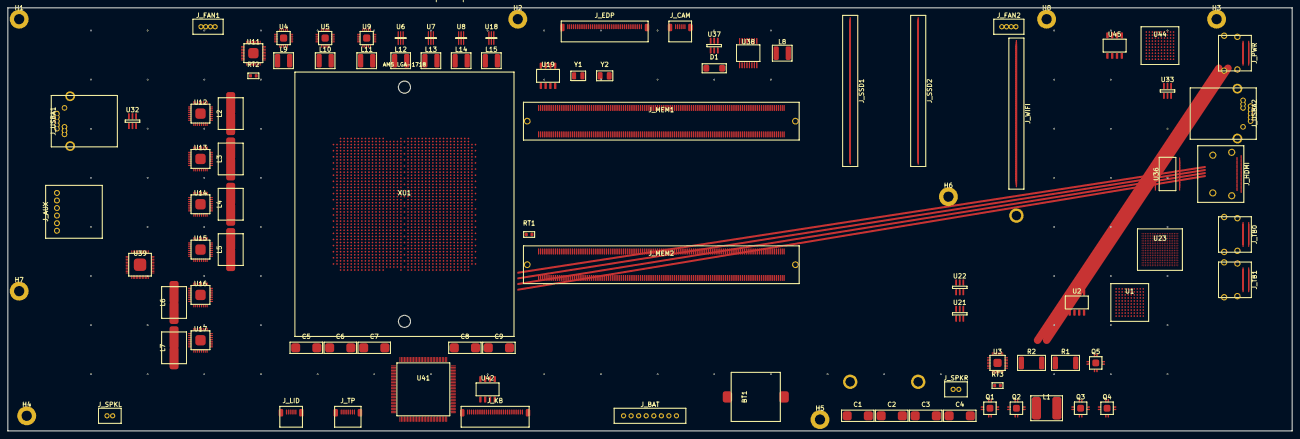
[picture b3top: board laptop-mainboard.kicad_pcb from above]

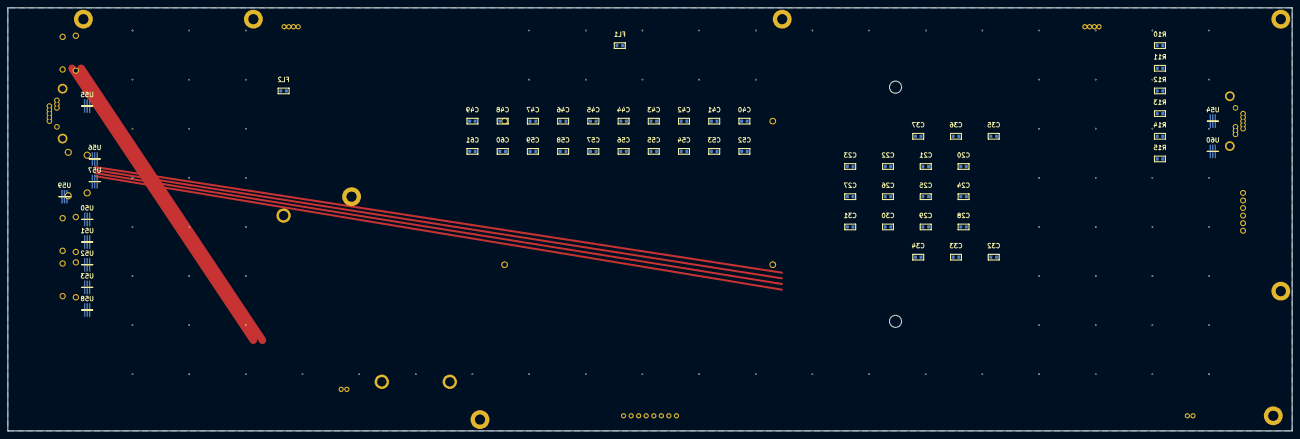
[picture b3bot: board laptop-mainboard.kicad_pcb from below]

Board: 8 copper layers, 340.0 x 112.0 mm, 157 parts (57 on the bottom side), 7 nets.

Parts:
BT1: ML1220; COIN_ML1220
C1, C2, C3, C4: 330u; CAP_7343
C5, C6, C7, C8, C9: 470u; CAP_7343
C20, C21, C22, C23, C24, C25, C26, C27, C28, C29, C30, C31, C32, C33, C34, C35, C36, C37: 22u; R_0603
C40, C41, C42, C43, C44, C45, C46, C47, C48, C49: 10u; R_0603
C52, C53, C54, C55, C56, C57, C58, C59, C60, C61: 100n; R_0603
D1: SS3P4; SMA_DIODE
FL1: CMC Webcam; R_0603
FL2: CMC WLAN; R_0603
H1, H2, H3, H4, H5, H6, H7, H8: MTG_M2_5
J_AUX: Klinke; TRRS_35
J_BAT: HP-Akku 3S 56Wh; CONN_BAT8_2mm
J_CAM: Webcam; FPC6_05
J_EDP: eDP-Panel; FPC40_05
J_FAN1: Luefter L; CONN_FAN4
J_FAN2: Luefter R; CONN_FAN4
J_HDMI: HDMI 2.1; HDMI_A
J_KB: HP-Tastatur; FPC30_05
J_LID: Lid-Sensor; FPC6_05
J_MEM1: DDR5 SO-DIMM A; SODIMM_DDR5_262
J_MEM2: DDR5 SO-DIMM B; SODIMM_DDR5_262
J_PWR: USB-C Ladeport 100W; USBC_24
J_SPKL: Spk L; CONN_SPK2
J_SPKR: Spk R; CONN_SPK2
J_SSD1, J_SSD2: NVMe Gen4 x4; M2_M_2280
J_TB0, J_TB1: USB-C TB4; USBC_24
J_TP: HP-Clickpad; FPC8_05
J_USBA1, J_USBA2: USB-A 5G; USBA3_TH
J_WIFI: WLAN/BT; M2_E_2230
L1: 3u3; IND_7x7
L2, L3, L4, L5, L6, L7: 220n; IND_7x7
L8: 10u; IND_4x4
L9, L10, L11: 1u; IND_4x4
L12, L13, L14, L15: 470n; IND_4x4
Q1, Q2, Q3, Q4: SiSS22DN; PowerPAK_1212
Q5: BATFET; PowerPAK_1212
R1, R2: 10m; R_2512
R10, R11, R12, R13, R14, R15: 10k; R_0603
RT1: NTC CPU; R_0603
RT2: NTC VRM; R_0603
RT3: NTC CHG; R_0603
U1: TPS65988 PD; BGA96_9x9
U2: PD-Cfg; SOIC8
U3: BQ25731; QFN32_4x4
U4: 5V Buck; QFN20_3x4
U5: 3V3 Buck; QFN20_3x4
U6: 1V8; DFN6_2x2
U7: 1V05_TB; DFN6_2x2
U8: 0V88_TB; DFN6_2x2
U9: 3V3_ALW; QFN20_3x4
U11: MP2857; QFN40_5x5
U12: Stage CPU1; QFN31_5x5
U13: Stage CPU2; QFN31_5x5
U14: Stage CPU3; QFN31_5x5
U15: Stage CPU4; QFN31_5x5
U16: Stage SOC1; QFN31_5x5
U17: Stage SOC2; QFN31_5x5
U18: 1V1_MEM; DFN6_2x2
U19: W25Q256JW; SOIC8
U21: SSD1-SW; SOT23-5
U22: SSD2-SW; SOT23-5
U23: JHL8540 TB4; BGA_10x9_JHL8540
U32, U33: VBUS-SW; SOT23-5
U36: TPD12S016; TSSOP24
U37: VLCD-SW; SOT23-5
U38: MP3389 BL; TSSOP16EP
U39: ALC256; QFN48_6x6
U41: IT5570E EC; LQFP128_14x14
U42: EC-Flash; SOIC8
U44: TPS65987D Ladeport; BGA96_9x9
U45: PD2-Cfg; SOIC8
U50: ESD TB0-L1; DFN6_2x2
U51: ESD TB0-L2; DFN6_2x2
U52: ESD TB1-L1; DFN6_2x2
U53: ESD TB1-L2; DFN6_2x2
U54: ESD USBA1; DFN6_2x2
U55: ESD USBA2; DFN6_2x2
U56: ESD HDMI-1; DFN6_2x2
U57: ESD HDMI-2; DFN6_2x2
U58: ESD CC; DFN6_2x2
U59: ESD TB-USB2; DFN6_2x2
U60: ESD A-USB2; DFN6_2x2
XU1: Ryzen 5 8600G; AM5_Socket_LGA1718
Y1: 32.768k; XTAL_3215
Y2: 48M; XTAL_3225

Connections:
+1V1_MEM: XU1.L19, XU1.L20, XU1.L23, XU1.L24, XU1.L25, XU1.L26, XU1.L27, XU1.L28, XU1.L29, XU1.L30, XU1.M20, XU1.M24, XU1.M26, XU1.M28, XU1.M29, XU1.N19, XU1.N23, XU1.N25, XU1.N27, XU1.P22, XU1.P24, XU1.P26, XU1.P28
+1V8: XU1.AN9, XU1.AN11, XU1.AP7, XU1.AP8, XU1.AP10, XU1.AP11, XU1.AP13, XU1.AP15, XU1.AP18, XU1.AP19, XU1.AP20, XU1.AR8, XU1.AR12, XU1.AR14, XU1.AR19, XU1.AT7, XU1.AT8, XU1.AT9, XU1.AT10, XU1.AT11, XU1.AT12, XU1.AT13, XU1.AT14, XU1.AT15, XU1.AT18, XU1.AT19
+VDDCR_CPU: XU1.AA7, XU1.AA8, XU1.AA10, XU1.AA12, XU1.AA14, XU1.AA16, XU1.AA18, XU1.AA20, XU1.AA22, XU1.AA24, XU1.AA26, XU1.AA28, XU1.AA29, XU1.AB7, XU1.AB8, XU1.AB13, XU1.AB15, XU1.AB17, XU1.AB19, XU1.AB21, XU1.AB23, XU1.AB25, XU1.AB27, XU1.AC7, XU1.AC8, XU1.AC10, XU1.AC12, XU1.AC14, XU1.AC18, XU1.AC20, XU1.AC22, XU1.AC24, XU1.AC26, XU1.AC28, XU1.AD7, XU1.AD8, XU1.AD11, XU1.AD15, XU1.AD17, XU1.AD19, XU1.AD23, XU1.AD25, XU1.AD27, XU1.AD29, XU1.AE8, XU1.AE10, XU1.AE16, XU1.AE18, XU1.AE20, XU1.AE22, XU1.AE24, XU1.AE26, XU1.AE28, XU1.AE29, XU1.AF7, XU1.AF8, XU1.AF11, XU1.AF13, XU1.AF15, XU1.AF17, XU1.AF19, XU1.AF23, XU1.AF25, XU1.AF27, XU1.AF30, XU1.AG7, XU1.AG8, XU1.AG12, XU1.AG14, XU1.AG16, XU1.AG18, XU1.AG20, XU1.AG22, XU1.AG24, XU1.AG26, XU1.AG28, XU1.AG29, XU1.AH7, XU1.AH8, XU1.AH10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
+VDDCR_SOC: XU1.L8, XU1.L9, XU1.L10, XU1.L11, XU1.L12, XU1.L13, XU1.L14, XU1.L15, XU1.L16, XU1.L17, XU1.L18, XU1.M8, XU1.M10, XU1.M12, XU1.M14, XU1.M16, XU1.M18, XU1.N11, XU1.N15, XU1.N17, XU1.P10, XU1.P12, XU1.P14, XU1.P16
GND: XU1.A4, XU1.A8, XU1.A9, XU1.A11, XU1.A13, XU1.A15, XU1.A20, XU1.A23, XU1.A25, XU1.A28, XU1.A31, XU1.A34, XU1.A37, XU1.AA1, XU1.AA4, XU1.AA5, XU1.AA11, XU1.AA15, XU1.AA17, XU1.AA19, XU1.AA23, XU1.AA25, XU1.AA27, XU1.AA30, XU1.AA32, XU1.AA35, XU1.AA37, XU1.AA38, XU1.AA41, XU1.AB2, XU1.AB3, XU1.AB4, XU1.AB5, XU1.AB6, XU1.AB10, XU1.AB14, XU1.AB16, XU1.AB18, XU1.AB20, XU1.AB22, XU1.AB24, XU1.AB26, XU1.AB28, XU1.AB29, XU1.AB31, XU1.AB33, XU1.AB36, XU1.AB39, XU1.AC3, XU1.AC6, XU1.AC9, XU1.AC11, XU1.AC13, XU1.AC17, XU1.AC19, XU1.AC21, XU1.AC23, XU1.AC25, XU1.AC27, XU1.AC29, XU1.AC31, XU1.AC33, XU1.AC36, XU1.AC39, XU1.AD1, XU1.AD3, XU1.AD4, XU1.AD5, XU1.AD12, XU1.AD14, XU1.AD16, XU1.AD18, XU1.AD20, XU1.AD22, XU1.AD24, XU1.AD26, XU1.AD28, XU1.AD30, XU1.AD32, XU1.AD35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
VDD_18_S5: XU1.AR20, XU1.AT20
VDD_MISC_S5: XU1.AP17, XU1.AT16, XU1.AT17

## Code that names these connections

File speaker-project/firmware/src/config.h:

// SpeakerBox Pro — Pin-Zuordnung und Konstanten.
// Muss mit pcb/main-board/design.py uebereinstimmen!
#pragma once

// --- GPIO-Zuordnung (ESP32-S3-WROOM-1) --------------------------------------
#define PIN_PWR_HOLD    4    // NPN-Latch: high = Versorgung halten
#define PIN_BTN_PWR     5    // Power-Taster (low-aktiv, 10k Pullup extern)
#define PIN_BTN_ADC     6    // Widerstandsleiter der 5 Funktionstasten
#define PIN_VBAT_SENSE  7    // Akkuspannung ueber 100k/10k-Teiler
#define PIN_AMP_SDZ     15   // TPA3118 Shutdown (high = Verstaerker an)
#define PIN_LED_DATA    16   // WS2812B auf Button-Board
#define PIN_BT_TX       17   // UART1 TX -> BT-Modul RX
#define PIN_BT_RX       18   // UART1 RX <- BT-Modul TX
#define PIN_I2C_SDA     8
#define PIN_I2C_SCL     9
#define PIN_BT_EN       3    // BT-Modul Enable
#define PIN_BT_STATUS   10   // BT-Modul Status-Ausgang (high = verbunden)
#define PIN_BT_PAIR     11   // BT-Modul Pairing-Taste (Impuls)
#define PIN_CHG_STAT    12   // Lade-Board: laedt (low-aktiv, open-drain)
#define PIN_FULL_STAT   13   // Lade-Board: voll (low-aktiv)
#define PIN_AMP_MUTE    21   // TPA3118 Mute (high = stumm)
#define PIN_AMP_FAULT   47   // TPA3118 FAULTZ (low = Fehler)
#define PIN_DSP_NRST    48   // ADAU1701 Reset (low-aktiv)

// --- I2C-Adressen ------------------------------------------------------------
#define I2C_ADDR_DSP    0x34 // ADAU1701 (ADDR1=0, ADDR0=0 -> 0x68 >> 1)
#define I2C_ADDR_OLED   0x3C // SSD1306

// --- Akku (4S Li-Ion) ---------------------------------------------------------
#define VBAT_DIVIDER    11.0f   // (100k+10k)/10k
#define VBAT_FULL       16.8f
#define VBAT_EMPTY      12.0f
#define VBAT_WARN       13.2f   // Rot blinken unterhalb

// --- Verhalten -----------------------------------------------------------------
#define PWR_HOLD_MS     2000    // Taster 2 s halten = Ein-/Ausschalten
#define VOLUME_STEPS    50
#define WIFI_AP_SSID    "SpeakerBox-Pro"
#define DEVICE_NAME     "SpeakerBox Pro"
#define FW_VERSION      "1.0.0"

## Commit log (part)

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2026-05-29 Velo Navi Schweiz: Bike-/E-Bike-Navigation mit Routenvorschlägen, Höhen-/Zeitberechnung und Tempo-Feedback
    - Routing über BRouter (OSM) mit Profilen Trekking/Rennvelo/Gravel/MTB + Alternativrouten
    - Physikbasierte Zeitberechnung inkl. Steigung und Velo-Typ (Velo / E-Bike 25 / E-Bike 45, Motor-Abregelung)
    - Routenbeschreibung (Strasse/Veloweg/Schotter/Wald/Trail), Höhenmeter und Höhenprofil
    - Ortssuche und Karten über swisstopo/geo.admin.ch, Leaflet-Karte
    - Feedback nach Fahrt kalibriert Tempo pro Velo-Typ (localStorage)
    - GPX-Export
2026-05-29 Velo Navi Schweiz app
2026-05-29 GitHub Pages Deploy-Workflow hinzufügen
2026-05-29 Velo Navi Schweiz – Bike-/E-Bike-Navigation (#1)
    * Velo Navi Schweiz: Bike-/E-Bike-Navigation mit Routenvorschlägen, Höhen-/Zeitberechnung und Tempo-Feedback
    - Routing über BRouter (OSM) mit Profilen Trekking/Rennvelo/Gravel/MTB + Alternativrouten
    - Physikbasierte Zeitberechnung inkl. Steigung und Velo-Typ (Velo / E-Bike 25 / E-Bike 45, Motor-Abregelung)
    - Routenbeschreibung (Strasse/Veloweg/Schotter/Wald/Trail), Höhenmeter und Höhenprofil
    - Ortssuche und Karten über swisstopo/geo.admin.ch, Leaflet-Karte
    - Feedback nach Fahrt kalibriert Tempo pro Velo-Typ (localStorage)
2026-05-29 Pages-Deploy ausloesen (.nojekyll)
2026-05-29 Auf klassisches Pages (Deploy from branch) umstellen: Actions-Workflow entfernen
2026-05-29 Live-Navigation, Sprachführung, GPS-Standort und PWA hinzufügen
    - Vollbild-Navigationsmodus mit Turn-by-Turn-Anweisungen (aus Routengeometrie abgeleitet)
    - Sprachausgabe auf Deutsch (Web Speech API) mit Vorankuendigungen
    - Live-GPS (watchPosition): Positionsmarker, Restroute, ETA/Restzeit/Distanz/Tempo
    - Automatisches Rerouting bei Routenabweichung (>40m)
    - Wake Lock haelt Display an, Kompass fuer Richtungspfeil
    - 'Mein Standort'-Button als Start (GPS + Reverse-Geocoding)
2026-05-29 Bugfixes: Ziel/Start aus Texteingabe uebernehmen, Tausch behaelt Punkte, Karte setzt Punkt erst bei 1s Long-Press
    - Eingetippter Ort wird beim Verlassen des Feldes / Enter automatisch geokodiert und gesetzt (auch ohne Vorschlagsauswahl)
    - 'Routen berechnen' holt fehlende Punkte aus den Textfeldern nach
    - Tauschen behaelt beide Punkte korrekt
    - Kartenpunkt nur noch per 1-Sekunden-Long-Press (verhindert versehentliches Setzen beim Routenauswaehlen/Verschieben), mit visuellem Ring
    - Long-Press im Navi-Modus deaktiviert
2026-05-29 Long-Press auf 450ms verkuerzen und iOS-Auswahl-/Kopiermenue auf der Karte unterdruecken
    - Halte-Dauer 700ms -> 450ms (verhindert iOS-Text-Auswahlmenue)
    - -webkit-touch-callout/user-select none auf Karte
    - preventDefault auf mousedown, kurzes haptisches Feedback
    - SW-Cache auf v2 fuer Update
2026-05-29 SW-Cache v3
2026-05-29 Hoehenprofil adaptiv: Canvas fuellt Panel per Flexbox, km-Achse innerhalb gezeichnet, Neuzeichnen nach Layout/Resize
    - Canvas flex statt fixer Hoehe (unterer Teil wurde abgeschnitten)
    - Zeichnen nach Layout (requestAnimationFrame) + bei Resize
    - adaptive Paddings, km-Beschriftung mittig/innerhalb des Canvas
    - SW-Cache v3
2026-05-29 Ortssuche erweitern: Berge, Gipfel, Paesse, Seen/Fluesse, Flurnamen, Strassen, Quartiere
    - geo.admin.ch-Quellen erweitert (gazetteer, district, kantone) zusaetzlich zu Adressen/PLZ/Gemeinden
    - Kategorisierung mit Icons (Berg, See, Pass, Strasse, Gemeinde, Kanton ...)
    - technische Typ-Praefixe fuer saubere Labels entfernt
    - Platzhalter/Hinweise angepasst; SW-Cache v4
2026-05-29 SW-Cache v4

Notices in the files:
parts and their libraries:
AM5 LGA-1718, Pinbelegung nach WikiChip-Pinmap (Public Domain, Wikimedia Commons), Raster 0.94x0.81mm
